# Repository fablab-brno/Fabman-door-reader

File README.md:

# Fabman door reader

This repository is for Fabman door reader. This device and firmware were designed and developed by FabLab Brno. 

You can find here: 
 - PCB data for all revision of HW 
 - STL files for case
 - design files of the case for Fusion 360
 - source code of the firmware for this device 
 - images of assembled board and images of the case
 
We used Arduino IDE for development of this firmware. 

You will need these libraries to compile FW from source code: 
 - ArduinoJson (v. 6.13.0 in Library Manager)
 - WiFiManager (https://github.com/tzapu/WiFiManager/tree/development)- install it in IDE from ZIP file
 - SimpletTimer (https://github.com/jfturcot/SimpleTimer) - install it in IDE from ZIP file
 - SmartLeds (https://platformio.org/lib/show/1740/SmartLeds) - install it in IDE from ZIP file

#### This firmware include following:

- [x] OTA update
- [x] WiFiManager - you can setup your WiFi network for OTA updates, API key for Fabman bridge, name of the device, ID of the device and if connection type (WiFi/Ethernet) 

If somebody swipe their card and device is properly set to use Fabman service, it will send standart query and behave on received data. There is also option (which we use, but it is not default behaviour) to check, if member has **any** actvive package, and if so,it will be allowd to use door. This behaviour must be set by bollean variable (checkOH in config.h file) and FW must recompiled and flashed again in to the device. I will try to add this as option via WiFiManager in the future.  
OTA updates are available, but you must have some server where you can store text and bin files. Device check for new FW update at every start. 

#### HW include following: 

 - RGB LED (WS2812B) - which indicate status of the device (breathing blue - idle, green - allowed access, red - denied access, orange - WiFiManager setup process)
 - 12V to 5V voltage converter based on MP1584EN
 - 3-pin connector for 12V power connection (+12V, GND, GND for lock)
 - 2-pin connector for security alarm (optional). This is normaly closed when cover is closed as screw is pushing towards tactile switch. If somebody open the cover, switch will be released and external alarm system should trigger some alert.    
 - Security button
 - 3-pin JST connector for RFID data. This one is connected to the GWIOT 7941E RFID module which sends data via UART connection (9600 bauds). There is 5V, DATA and GND.  
 - 5V DC relay G6L-1F-DC5 which connect GND to the lock in the door. Positive voltage must be connected to the door directly.
 - 4-pin connector for UART. There is 5V, GND, RX and TX connection and this connector is used for programming and debugging.
 - Reset button
 - Boot button
 - Setup button - if you hold this button when device is powered on or reseted, it will call function which will turn on AP mode in ESP32 and will fire up web server with default address **192.168.4.1**. 

You can find some images of the board, 3D printed case and whole assembly in **/img** folder.
  
#### There are these revision of the board:

**rev. A**

First version of the board. Step-down converter is not working (wrong layout). RGB LED need bodge wire to the IO4 on ESP32. Everything else is working. 

**rev. B** 

Step-down converter is now using reference design for MP1584EN. RGB LED connection fixed. Relay and 3-pin JST connector moved to bottom side to save some height. Added setup button for WiFiManager. Added 6-pin connector to connect LAN module via SPI bus. This was working but LAN module (ENC28J60) does not supprt SSL connection.

**rev. C**

6-pin connector changed for 14-pin connector which support LAN8720 module. This module is supported by Arduino-ESP32 development tools. This as tested and it is working. **This board does not support PoE**.

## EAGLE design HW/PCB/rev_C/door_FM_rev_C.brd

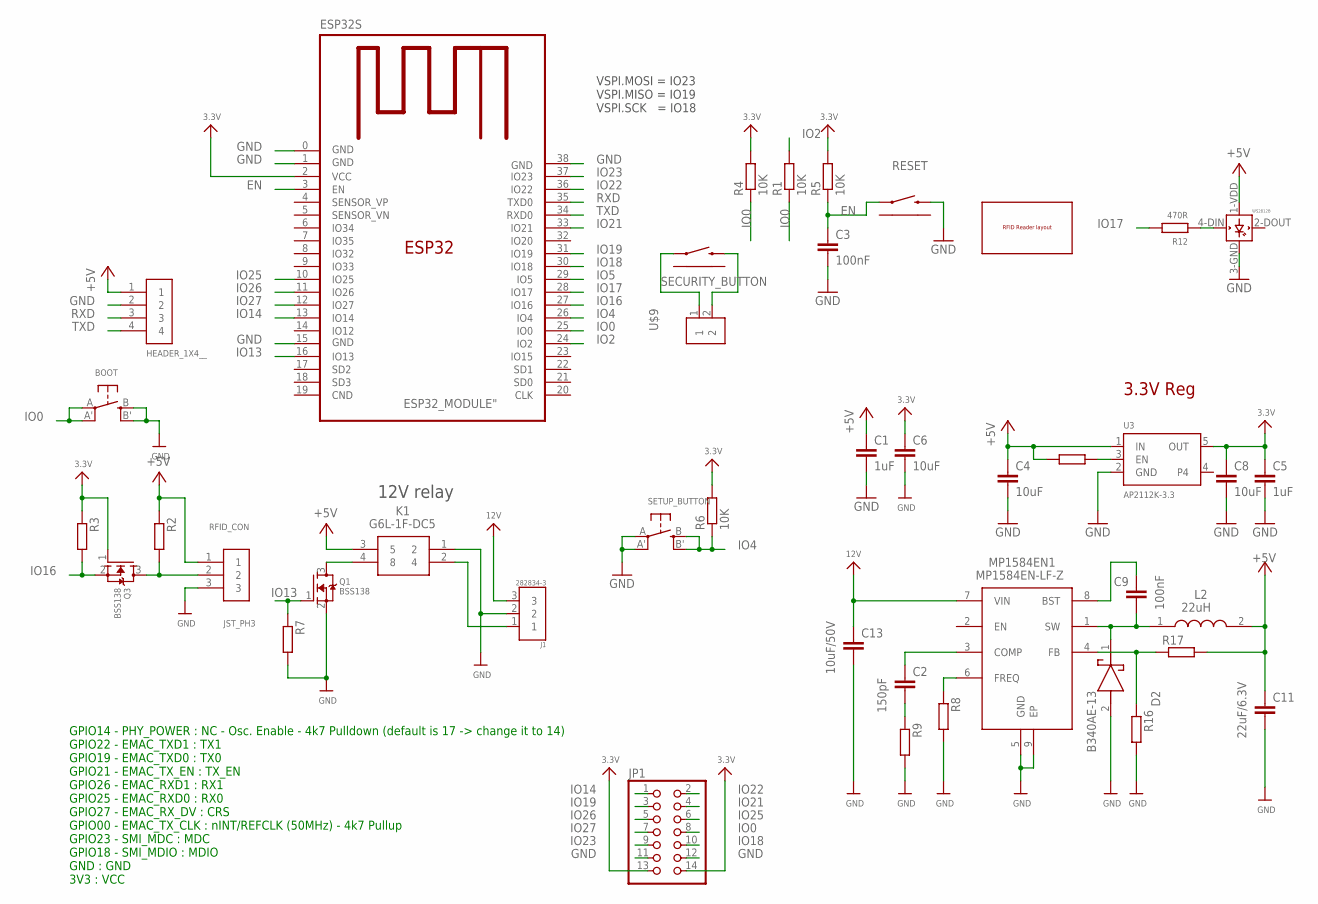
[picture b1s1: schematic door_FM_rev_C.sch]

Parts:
BOOT: BUTTON_KMR2_4.6X2.8
C1, C5: 1uF; C0805
C2: 150pF; C0805
C3, C9: 100nF; C0805
C4, C6, C8: 10uF; C0805
C11: 22uF/6.3V; C0805
C13: 10uF/50V; C1206
CN1: HEADER_1X4__; HEADER_1X4_RIGHT_ANGLE
D2: B340AE-13; DIOM5226X240N
ESP32S: ESP32_MODULE"; ESP32_MODULE
J1: 282834-3; TE_282834-3
JP1: PINHD-2X7SMT; 2X07_SMT
K1: G6L-1F-DC5
L2: 22uH; ASPI-0630LR
MP1584EN1: MP1584EN-LF-Z; SOIC127P600X170-9N
Q1, Q3: BSS138; SOT95P240X110-3
R1, R2, R3, R4, R5, R6, R7, R19: 10K; R0805
R8, R9: 100K; R0805
R12: 470R; R0805
R16: 40K2; R0805
R17: 210K; R0805
RESET: TACTILE_SWITCH_RIGHT_ANGLE_THT_; TACTILE_SWITCH_RIGHT_ANGLE_THT
RFID_CON: JST_PH3; JST-PH3
SECURITY_BUTTON: TACTILE_SWITCH_RIGHT_ANGLE_THT_; TACTILE_SWITCH_RIGHT_ANGLE_THT
SETUP_BUTTON: BUTTON_KMR2_4.6X2.8
U3: AP2112K-3.3; SOT95P290X120-5
U$9: 282834-2; CONN_282834-2
U$10: RFID_READER
WS2812B: WS2812B__; WS2812B_5050

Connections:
3.3V: C5.1, C6.1, C8.1, ESP32S.2 (VCC), JP1.13, JP1.14, Q3.1 (G), R3.1, R4.2, R5.2, R6.2, U3.5 (OUT)
12V: C13.1, J1.3, MP1584EN1.7 (VIN)
+5V: C1.1, C4.1, C11.1, CN1.1, K1.3 (5), L2.2, R2.1, R17.2, R19.1, RFID_CON.1, U3.1 (IN), WS2812B.1-VDD (VDD)
EN: C3.1, ESP32S.3 (EN), R5.1, RESET.1
GND: BOOT.B (S), BOOT.B' (S1), C1.2, C3.2, C4.2, C5.2, C6.2, C8.2, C11.2, C13.2, CN1.2, D2.2 (A), ESP32S.0 (GND), ESP32S.1 (GND), ESP32S.15 (GND), ESP32S.38 (GND), J1.2, JP1.11, JP1.12, K1.1 (2), MP1584EN1.5 (GND), MP1584EN1.9 (EP), Q1.2 (S), R7.2, R8.2, R9.2, R16.2, RESET.2, RFID_CON.3, SETUP_BUTTON.A, SETUP_BUTTON.A' (P1), U3.2 (GND), WS2812B.3-GND (GND)
IO0: BOOT.A, BOOT.A' (P1), ESP32S.25 (IO0), JP1.8, R1.1, R4.1
IO2: ESP32S.24 (IO2), R1.2
IO4: ESP32S.26 (IO4), R6.1, SETUP_BUTTON.B (S), SETUP_BUTTON.B' (S1)
IO5: ESP32S.29 (IO5)
IO13: ESP32S.16 (IO13), Q1.1 (G), R7.1
IO14: ESP32S.13 (IO14), JP1.1
IO16: ESP32S.27 (IO16), Q3.2 (S), R3.2
IO17: ESP32S.28 (IO17), R12.2
IO18: ESP32S.30 (IO18), JP1.10
IO19: ESP32S.31 (IO19), JP1.3
IO21: ESP32S.33 (IO21), JP1.4
IO22: ESP32S.36 (IO22), JP1.2
IO23: ESP32S.37 (IO23), JP1.9
IO25: ESP32S.10 (IO25), JP1.6
IO26: ESP32S.11 (IO26), JP1.5
IO27: ESP32S.12 (IO27), JP1.7
unnamed: K1.4 (8), Q1.3 (D)
unnamed: SECURITY_BUTTON.1, U$9.1
unnamed: SECURITY_BUTTON.2, U$9.2
unnamed: J1.1, K1.2 (4)
unnamed: Q3.3 (D), R2.2, RFID_CON.2
unnamed: R12.1, WS2812B.4-DIN (DIN)
unnamed: MP1584EN1.6 (FREQ), R8.1
unnamed: C2.2, R9.1
unnamed: R19.2, U3.3 (EN)
unnamed: C2.1, MP1584EN1.3 (COMP)
unnamed: MP1584EN1.4 (FB), R16.1, R17.1
unnamed: C9.2, D2.1 (K), L2.1, MP1584EN1.1 (SW)
unnamed: C9.1, MP1584EN1.8 (BST)
RXD: CN1.3, ESP32S.35 (TXD0)
TXD: CN1.4, ESP32S.34 (RXD0)

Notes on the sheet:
VSPI.MOSI = IO23 VSPI.MISO = IO19 VSPI.SCK = IO18
12V relay
3.3V Reg
GPIO14 - PHY_POWER : NC - Osc. Enable - 4k7 Pulldown (default is 17 -> change it to 14) GPIO22 - EMAC_TXD1 : TX1 GPIO19 - EMAC_TXD0 : TX0 GPIO21 - EMAC_TX_EN : TX_EN GPIO26 - EMAC_RXD1 : RX1 GPIO25 - EMAC_RXD0 : RX0 GPIO27 - EMAC_RX_DV : CRS GPIO00 - EMAC_TX_CLK : nINT/REFCLK (50MHz) - 4k7 Pullup G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

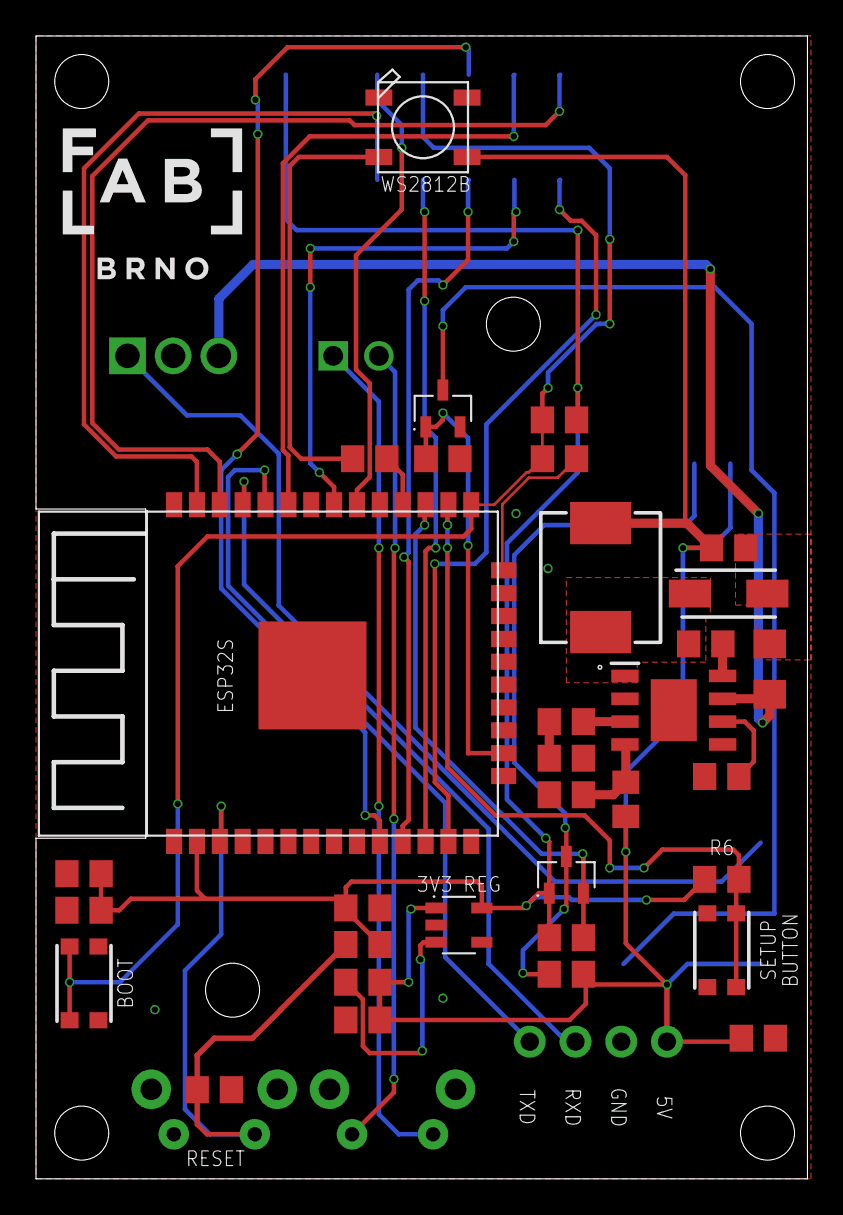
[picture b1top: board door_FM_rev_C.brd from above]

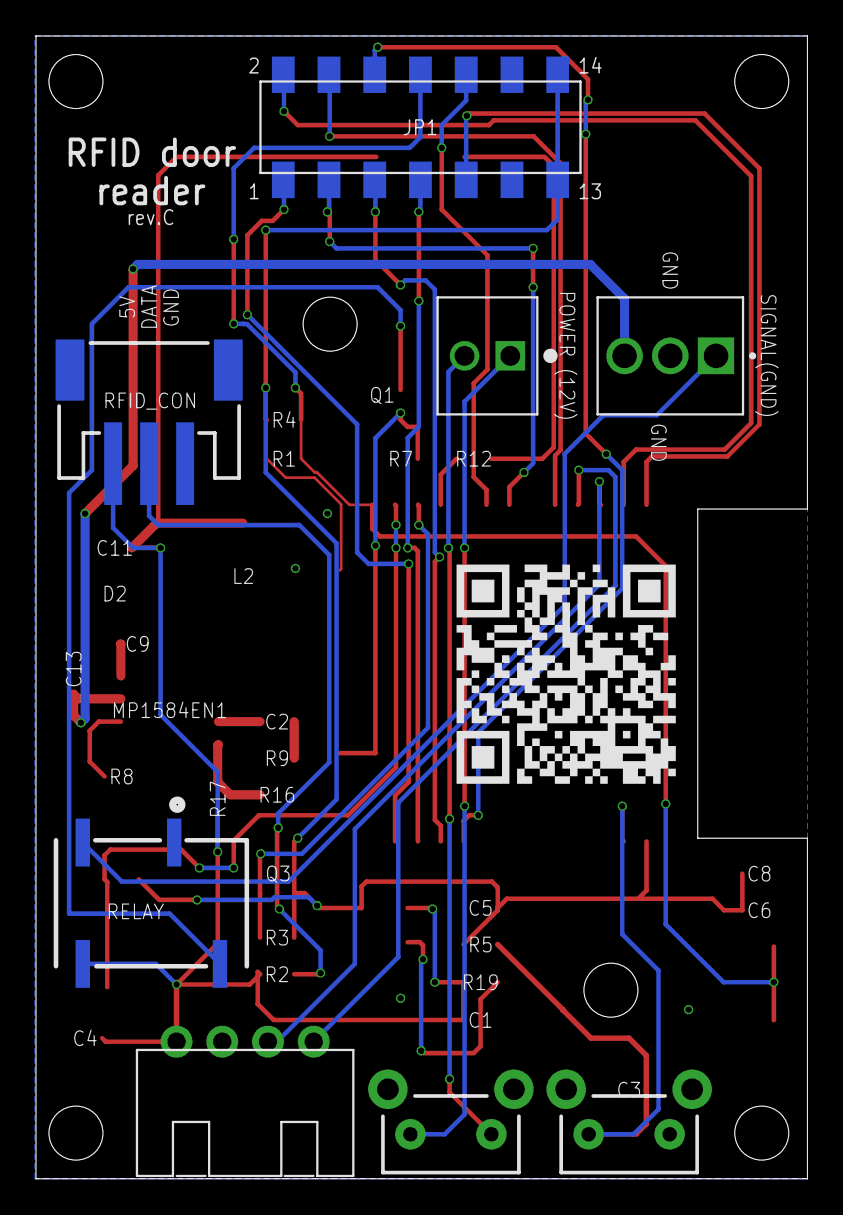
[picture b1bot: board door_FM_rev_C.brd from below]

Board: 2 copper layers, 42.9 x 63.5 mm, 42 parts (8 on the bottom side), 35 nets.

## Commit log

2020-06-22 Fix for typos
2020-06-22 FM door picture insert to the readme
2020-06-29 dded option to check if member has any active package & delete of some unused code
2020-07-02 Update
    - code cleanup
    - added function which will log who used the reader
    - added NTPClient for timestamps
    - added variables to hold member ID and machine ID
2020-09-04 Ethernet implementation
2020-09-08 Added custom callbacks for setting up FM device
    - wifi settings
    - name of the bridge
    - ID of the bridge
    - bool for settings wifi or ethernet
2020-09-29 Readme update and added rev.C Eagle files
2020-09-30 Added pictures

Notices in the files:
parts and their libraries:
microbuilder: This work is placed in the public domain, and may be freely used for commercial and non-commercial work with the following conditions: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
